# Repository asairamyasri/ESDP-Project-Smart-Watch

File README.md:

# Ultra-Low-Power ESP32 Smartwatch

## Overview
This project is an ESP32-based smartwatch using an E-Ink display for low-power wearable applications. 

## Features
- ESP32 microcontroller
- E-Ink display
- Low-power operation
- Real-time clock support
- Custom watch faces
- Battery-powered wearable system

## Team Members
- A Sai Ramya Sri (EE24BTECH11202)
- JLB Saraswathi (EE24BTECH11209)
- K Lakshmi Pranavi (EE24BTECH11210)
- Lakshitha Totakura (EE24BTECH11214)
- P Devi Amrutha (EE24BTECH11219)
## Project Structure
proposal/
bom/
hardware design/
software code/
current status/

## Hardware
The hardware section includes:
- Schematic design
- PCB layout
- Gerber files

## Software
The software section contains:
-GPIO Mapping: Hardware configuration for the ESP32-S3.
-Hardware tests: Firmware for component testing and bring-up.
-Driver Logic: Low-power E-Ink and battery management.
## Current Status

- [x] Create a Proposal
- [x] Prepare the BOM
- [x] Draw the schematic
- [x] PCB Layout
- [x] Generate Gerber Files
- [x] Order PCB on PCB Power
- [x] Design a case for the PCB
- [x] Develop Firmware
- [x] Receive PCB
- [ ] Firmware Integration
- [ ] Hardware Debugging if any

## Ongoing Work
Testing firmware on the PCB.

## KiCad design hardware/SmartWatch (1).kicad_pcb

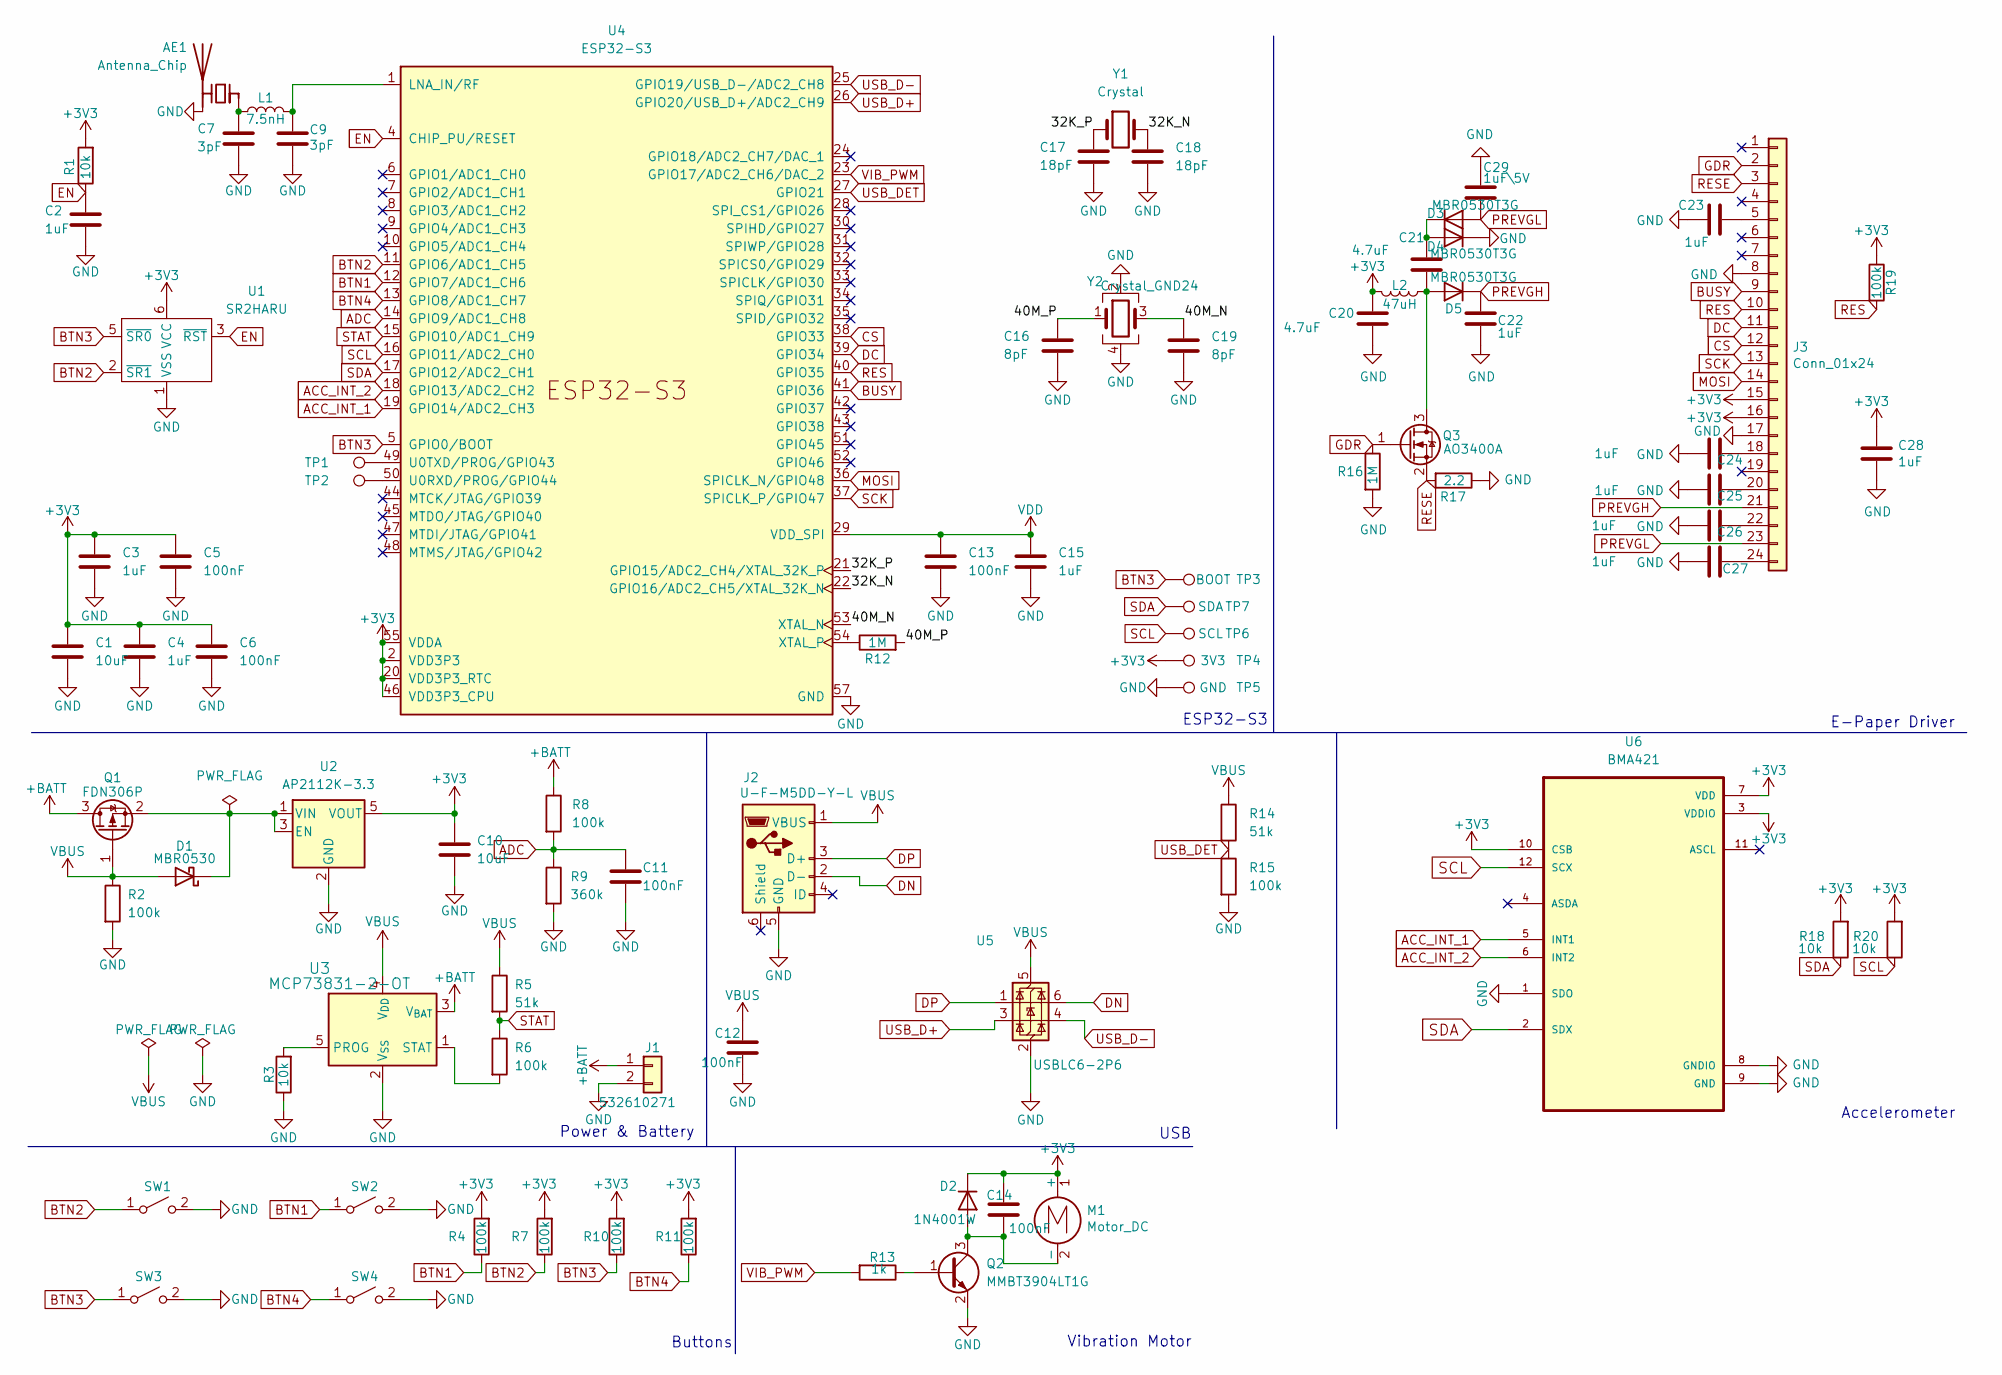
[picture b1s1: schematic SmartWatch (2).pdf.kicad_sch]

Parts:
AE1: Antenna_Chip; SWRA117D
C1, C10: 10uF; C_0402_1005Metric
C2, C3, C4, C15, C22, C23, C24, C25, C26, C27, C28: 1uF; C_0402_1005Metric
C5, C6, C11, C12, C13, C14: 100nF; C_0402_1005Metric
C7, C9: 3pF; C_0402_1005Metric
C16, C19: 8pF; C_0402_1005Metric
C17, C18: 18pF; C_0402_1005Metric
C20, C21: 4.7uF; C_0603_1608Metric
C29: 1uF\5V; C_0402_1005Metric
D1: MBR0530; DIO_MBR0530T3G
D2: 1N4001W; D_SOD-123F
D3, D4, D5: MBR0530T3G; DIO_MBR0530T3G
J1: 532610271; 1.25T-2PWT (Molex 532610271)
J2: U-F-M5DD-Y-L; USB_Micro-B
J3: Conn_01x24; 24_Pins_0.5mm_Pitch_ZIF_Connector_UP
L1: 7.5nH; L_0402_1005Metric
L2: 47uH; L_Taiyo-Yuden_NR-40xx
M1: Motor_DC; Motor_Header
Q1: FDN306P; SOT-23
Q2: MMBT3904LT1G; SOT-23
Q3: AO3400A; SOT-23
R1, R3, R18, R20: 10k; R_0402_1005Metric
R2, R4, R6, R7, R8, R10, R11, R15, R19: 100k; R_0402_1005Metric
R5, R14: 51k; R_0402_1005Metric
R9: 360k; R_0402_1005Metric
R12, R16: 1M; R_0402_1005Metric
R13: 1k; R_0402_1005Metric
R17: 2.2; R_0402_1005Metric
SW1, SW2, SW3, SW4: BTN3; TS24CA
TP1: TX; TestPoint_Pad_D1.0mm
TP2: RX; TestPoint_Pad_D1.0mm
TP3: BOOT; TestPoint_Pad_D1.0mm
TP4: 3V3; TestPoint_Pad_D1.0mm
TP5: GND; TestPoint_Pad_D1.0mm
TP6: SCL; TestPoint_Pad_D1.0mm
TP7: SDA; TestPoint_Pad_D1.0mm
U1: SR2HARU; sr2haru
U2: AP2112K-3.3; SOT-23-5
U3: MCP73831-2-OT; SOT-23-5
U4: ESP32-S3; QFN-56-1EP_7x7mm_P0.4mm_EP5.6x5.6mm
U5: USBLC6-2P6; SOT-666
U6: BMA421; LGA-12_2x2mm_P0.5mm
Y1: Crystal; Crystal_SMD_2012-2Pin_2.0x1.2mm
Y2: Crystal_GND24; Crystal_SMD_2520-4Pin_2.5x2.0mm

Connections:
+3V3: C1.1, C3.1, C4.1, C5.1, C6.1, C10.1, C14.1, C20.1, C28.1, D2.1 (K), J3.15, J3.16, L2.2, M1.1 (+), R1.2, R4.2, R7.2, R10.2, R11.2, R18.2, R19.1, R20.2, TP4.1, U1.6 (VCC), U2.5 (VOUT), U4.2 (VDD3P3), U4.3 (VDD3P3), U4.20 (VDD3P3_RTC), U4.46 (VDD3P3_CPU), U4.55 (VDDA), U4.56 (VDDA), U6.3 (VDDIO), U6.7 (VDD), U6.10 (CSB); also elsewhere on the board
+BATT: J1.1, Q1.3 (D), R8.1, U3.3 (V_{BAT})
/32K_N: C18.1, U4.22 (GPIO16/ADC2_CH5/XTAL_32K_N), Y1.2
/32K_P: C17.1, U4.21 (GPIO15/ADC2_CH4/XTAL_32K_P), Y1.1
/40M_N: C19.1, U4.53 (XTAL_N), Y2.3
/40M_P: C16.1, R12.2, Y2.1
ACC_INT_1: U4.19 (GPIO14/ADC2_CH3), U6.5 (INT1)
ACC_INT_2: U4.18 (GPIO13/ADC2_CH2), U6.6 (INT2)
ADC: C11.1, R8.2, R9.1, U4.14 (GPIO9/ADC1_CH8)
BTN1: R4.1, SW2.1 (A), U4.12 (GPIO7/ADC1_CH6)
BTN2: R7.1, SW1.1 (A), U1.2 (~SR1), U4.11 (GPIO6/ADC1_CH5)
BTN3: R10.1, SW3.1 (A), TP3.1, U1.5 (~SR0), U4.5 (GPIO0/BOOT)
BTN4: R11.1, SW4.1 (A), U4.13 (GPIO8/ADC1_CH7)
BUSY: J3.9, U4.41 (GPIO36)
CS: J3.12, U4.38 (GPIO33)
DC: J3.11, U4.39 (GPIO34)
DN: J2.2 (D-), U5.6 (I/O1)
DP: J2.3 (D+), U5.1 (I/O1)
EN: C2.1, R1.1, U1.3 (~RST), U4.4 (CHIP_PU/RESET)
GDR: J3.2, Q3.1 (G), R16.1
GND: AE1.2 (PCB_Trace), C1.2, C2.2, C3.2, C4.2, C5.2, C6.2, C7.2, C9.2, C10.2, C11.2, C12.2, C13.2, C15.2, C16.2, C17.2, C18.2, C19.2, C20.2, C22.2, C23.2, C24.2, C25.2, C26.2, C27.2, C28.2, C29.1, D4.1 (K), J1.2, J2.5 (GND), J3.8, J3.17, Q2.2 (E), R2.2, R3.1, R9.2, R15.2, R16.2, R17.1, SW1.2 (B), SW1.MP, SW2.2 (B), SW2.MP, SW3.2 (B), SW3.MP, SW4.2 (B), SW4.MP, TP5.1, U1.1 (VSS), U2.2 (GND), U3.2 (V_{SS}), U4.57 (GND), U5.2 (GND), U6.1 (SDO), U6.8 (GNDIO), U6.9 (GND), Y2.2, Y2.4; also elsewhere on the board
MOSI: J3.14, U4.36 (SPICLK_N/GPIO48)
unnamed: AE1.1 (FEED), C7.1, L1.1
unnamed: D1.1 (K), Q1.2 (S), U2.1 (VIN), U2.3 (EN)
unnamed: C14.2, D2.2 (A), M1.2 (-), Q2.3 (C)
unnamed: C21.1, D3.1 (K), D4.2 (A)
unnamed: C21.2, D5.2 (A), L2.1, Q3.3 (D)
unnamed: C23.1, J3.5
unnamed: C24.1, J3.18
unnamed: C25.1, J3.20
unnamed: C26.1, J3.22
unnamed: C27.1, J3.24
unnamed: Q2.1 (B), R13.1
unnamed: R3.2, U3.5 (PROG)
unnamed: R6.2, U3.1 (STAT)
unnamed: C9.1, L1.2, U4.1 (LNA_IN/RF)
unnamed: TP2.1, U4.50 (U0RXD/PROG/GPIO44)
unnamed: TP1.1, U4.49 (U0TXD/PROG/GPIO43)
unnamed: R12.1, U4.54 (XTAL_P)
PREVGH: C22.1, D5.1 (K), J3.21
PREVGL: C29.2, D3.2 (A), J3.23
RES: J3.10, R19.2, U4.40 (GPIO35)
RESE: J3.3, Q3.2 (S), R17.2
SCK: J3.13, U4.37 (SPICLK_P/GPIO47)
SCL: R20.1, TP6.1, U4.16 (GPIO11/ADC2_CH0), U6.12 (SCX)
SDA: R18.1, TP7.1, U4.17 (GPIO12/ADC2_CH1), U6.2 (SDX)
STAT: R5.2, R6.1, U4.15 (GPIO10/ADC1_CH9)
USB_D+: U4.26 (GPIO20/USB_D+/ADC2_CH9), U5.3 (I/O2)
USB_D-: U4.25 (GPIO19/USB_D-/ADC2_CH8), U5.4 (I/O2)
USB_DET: R14.2, R15.1, U4.27 (GPIO21)
VBUS: C12.1, D1.2 (A), J2.1 (VBUS), Q1.1 (G), R2.1, R5.1, R14.1, U3.4 (V_{DD}), U5.5 (VBUS)
VDD: C13.1, C15.1, U4.29 (VDD_SPI)
VIB_PWM: R13.2, U4.23 (GPIO17/ADC2_CH6/DAC_2)

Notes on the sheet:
Vibration Motor
Buttons
E-Paper Driver
Accelerometer
ESP32-S3
USB
Power & Battery

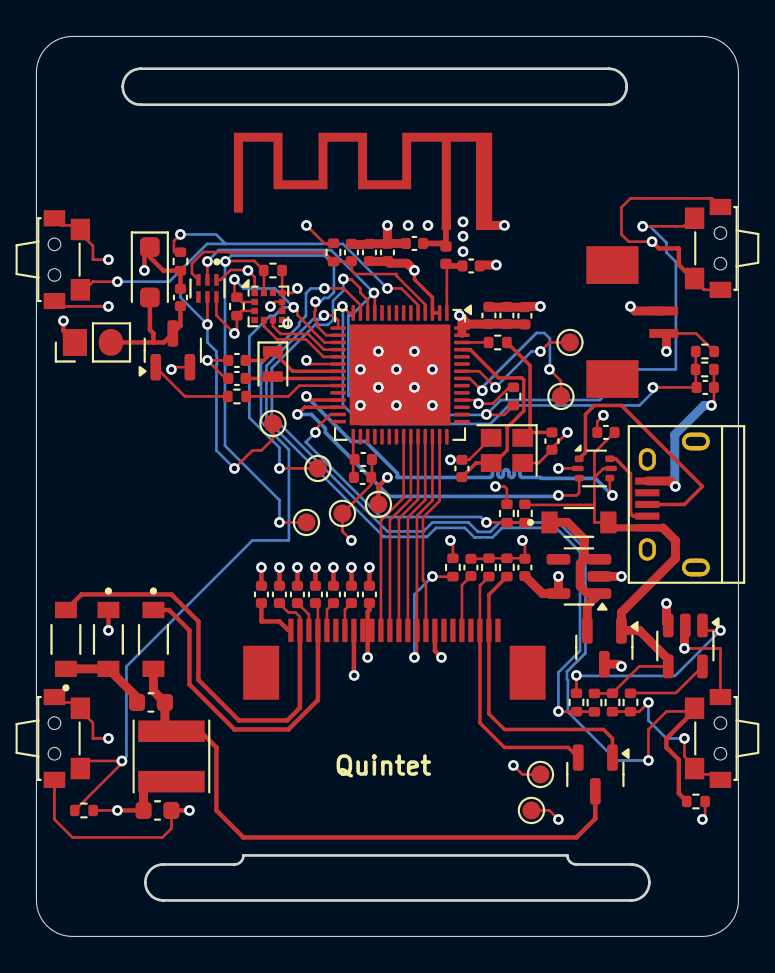
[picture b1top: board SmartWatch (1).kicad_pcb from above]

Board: 4 copper layers, 39.0 x 50.0 mm, 84 parts (0 on the bottom side), 53 nets.

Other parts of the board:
TP4#2: 3V3; TestPoint_Pad_D1.0mm
TP5#2: GND; TestPoint_Pad_D1.0mm

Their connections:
+3V3: TP4#2.1; also elsewhere on the board
GND: TP5#2.1; also elsewhere on the board

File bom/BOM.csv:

Id;Designator;Footprint;Quantity;Designation;MPN;Datasheet Link
1;C22,C24,C26,C15,C4,C2,C3,C25,C23,C28,C27,C29;C_0402_1005Metric;12;1uF;C0402C105K4PACTU;https://www.mouser.in/datasheet/3/72/1/C0402C105K4PACTU.pdf
2;R19,R4,R11,R2,R6,R15,R10,R7,R8;R_0402_1005Metric;9;100k;AC0402FR-07100KL ;https://www.mouser.in/datasheet/3/508/1/PYU_AC_51_ROHS_L.pdf
3;R1,R20,R3,R18;R_0402_1005Metric;4;10k;RC0402FR-0710KL ;https://www.mouser.com/catalog/specsheets/YAGEO_PYu_RC_Group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
4;Y1;Crystal_SMD_2012-2Pin_2.0x1.2mm;1;Crystal;ABS07-32.768KHZ-T ;https://www.mouser.in/datasheet/3/184/1/ABS07.pdf
5;C6,C11,C5,C14,C12,C13;C_0402_1005Metric;6;100nF;0402B104J250NT;https://www.mouser.in/datasheet/3/317/1/WTC_MLCC_General_Pur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
6;C1,C10;C_0402_1005Metric;2;10uF;C0402B106M010T;https://www.holystonecaps.com/PDF/201612051328350.2017%20HCC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
7;Y2;Crystal_SMD_2520-4Pin_2.5x2.0mm;1;Crystal_GND24;XRCGB40M000F1S2FR0 ;https://pim.murata.com/asset/pim4/ceramicResonatorCrystalUni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
8;SW3,SW4,SW1,SW2;TS24CA;4;BTN3;TS24CA 250gf 013;https://www.lcsc.com/datasheet/C5373430.pdf?spm=wm.sxq.inf.g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
9;R12,R16;R_0402_1005Metric;2;1M;RC0402JR-071ML ;https://www.mouser.com/catalog/specsheets/YAGEO_PYu_RC_Group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
10;C7,C9;C_0402_1005Metric;2;3pF;TCC0402COG3R0C500AT ;https://www.lcsc.com/datasheet/C696883.pdf?spm=wm.sxq.inf.gg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
11;D1,D3,D5,D4;DIO_MBR0530T3G;4;MBR0530T3G;MBR0530-TP ;https://www.mouser.in/datasheet/3/225/1/MBR0520-MBR0580(SOD123).pdf
12;R9;R_0402_1005Metric;1;360k;AC0402FR-07360KL ;https://www.mouser.in/datasheet/3/508/1/PYU_AC_51_ROHS_L.pdf
13;Q2;SOT-23;1;MMBT3904LT1G;MMBT3904LT1G ;https://www.onsemi.com/pdf/datasheet/mmbt3904lt1-d.pdf
14;J3;24_Pins_0.5mm_Pitch_ZIF_Connector_UP;1;Conn_01x24;AFC07-S24ECA-00 ;https://www.lcsc.com/datasheet/C262643.pdf?spm=wm.sxq.inf.gg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
15;J1;1.25T-2PWT (Molex 532610271);1;532610271;532610271;https://www.molex.com/en-us/products/part-detail-pdf/5326102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
16;U2;SOT-23-5;1;AP2112K-3.3;AP2112K-3.3TRG1 ;https://www.mouser.in/datasheet/3/175/1/AP2112.pdf
17;J2;USB_Micro-B;1;U-F-M5DD-Y-L;U-F-M5DD-Y-L ;https://www.lcsc.com/datasheet/C91146.pdf?spm=wm.sxq.inf.ggs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
18;C21,C20;C_0603_1608Metric;2;4.7uF;GRM188Z71C475KE21D ;https://pim.murata.com/asset/pim4/ceramicCapacitorSMD/GRM188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
19;R14,R5;R_0402_1005Metric;2;51k;AC0402FR-0751KL ;https://www.mouser.in/datasheet/3/508/1/PYU_AC_51_ROHS_L.pdf
20;U5;SOT-666;1;USBLC6-2P6;USBLC6-2P6 ;https://www.st.com/resource/en/datasheet/usblc6-2.pdf
21;C19,C16;C_0402_1005Metric;2;8pF;GRM1555C1H8R0CA01D ;https://pim.murata.com/asset/pim4/ceramicCapacitorSMD/GRM155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
22;U4;QFN-56-1EP_7x7mm_P0.4mm_EP5.6x5.6mm;1;ESP32-S3;ESP32-S3FN8 ;https://documentation.espressif.com/esp32-s3_datasheet_en.pdf
23;Q3;SOT-23;1;CJ3400A;CJ3400A;https://evelta.com/content/datasheets/217-CJ3400A.pdf
24;D2;D_SOD-123F;1;1N4001W;1N4001W ;https://robu-prod-media.s3.ap-south-1.amazonaws.com/uploads/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
25;L2;L_Taiyo-Yuden_NR-40xx;1;47uH;NR4018T470M ;https://mm.digikey.com/Volume0/opasdata/d220001/medias/docus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
26;C17,C18;C_0402_1005Metric;2;18pF;GRM1555C1H180JA01D ;https://www.mouser.in/datasheet/3/76/1/GRM1555C1H180JA01-01A.pdf
27;M1;Motor_Header;1;Motor_DC;VC1020B111F ;https://www.vybronics.com/coin-vibration-motors/with-brushes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
28;L1;L_0402_1005Metric;1;7.5nH;LQG15HS7N5J02D ;https://www.mouser.in/datasheet/3/76/2/JELF243B_0010.pdf
29;U6;LGA-12_2x2mm_P0.5mm;1;BMA421;BMA421 ;https://files.pine64.org/doc/datasheet/pinetime/BST-BMA421-F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
30;R13;R_0402_1005Metric;1;1k;AC0402FR-071KL ;https://www.mouser.in/datasheet/3/508/1/PYU_AC_51_ROHS_L.pdf
31;U1;sr2haru;1;SR2HARU;SR2HARU ;https://www.st.com/resource/en/datasheet/sr2.pdf
32;U3;SOT-23-5;1;MCP73831-2-OT;MCP73831T-2ACI/OT;https://www.mouser.in/datasheet/3/282/1/MCP73831_Family_Data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
33;R17;R_0402_1005Metric;1;2.2;WR04W2R20FTL;https://www.mouser.in/datasheet/3/317/1/ASC_WR.pdf
34;Q1;SOT-23;1;FDN306P;FDN306P;https://www.onsemi.com/pdf/datasheet/fdn306p-d.pdf
;;;;;;
;;;;;;
;;;;;;
;;;;;;
;;;;;;
;; ;;;;

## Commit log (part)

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2026-05-09 Rename README.md to Schematic
2026-05-09 Update README with project overview and details
    Expanded project details including features, team members, and project structure.
2026-05-09 Create prop
2026-05-09 Create bom
2026-05-09 Create img
2026-05-09 Create software
2026-05-09 Add initial hardware test for motor and button
2026-05-09 Refactor GPIO mappings
2026-05-09 Add Display_Driver.h for WatchEngine class
2026-05-09 Implement Display Driver functionality
2026-05-09 Add main firmware with setup and loop functions
2026-05-09 Update software section in README.md
    Added GPIO Mapping, Diagnostic Suite, and Driver Logic to the software section.
2026-05-09 Fix typo in software section of README
2026-05-09 Clarify ongoing work details in README
